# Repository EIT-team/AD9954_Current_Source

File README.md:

# AD9954 communication library

Communication over a serial port to program Analog Devices AD9954 DDS chip.

Arduino source code in _/Program_AD9954_.

Sample MATLAB code for programming over Serial port in _sample_code.m_

Serial commands:

  _frequency xxxx_      frequency to program (Hz)

  _stim 1_              Starts injection
  
  _stim 0_              Stops injection

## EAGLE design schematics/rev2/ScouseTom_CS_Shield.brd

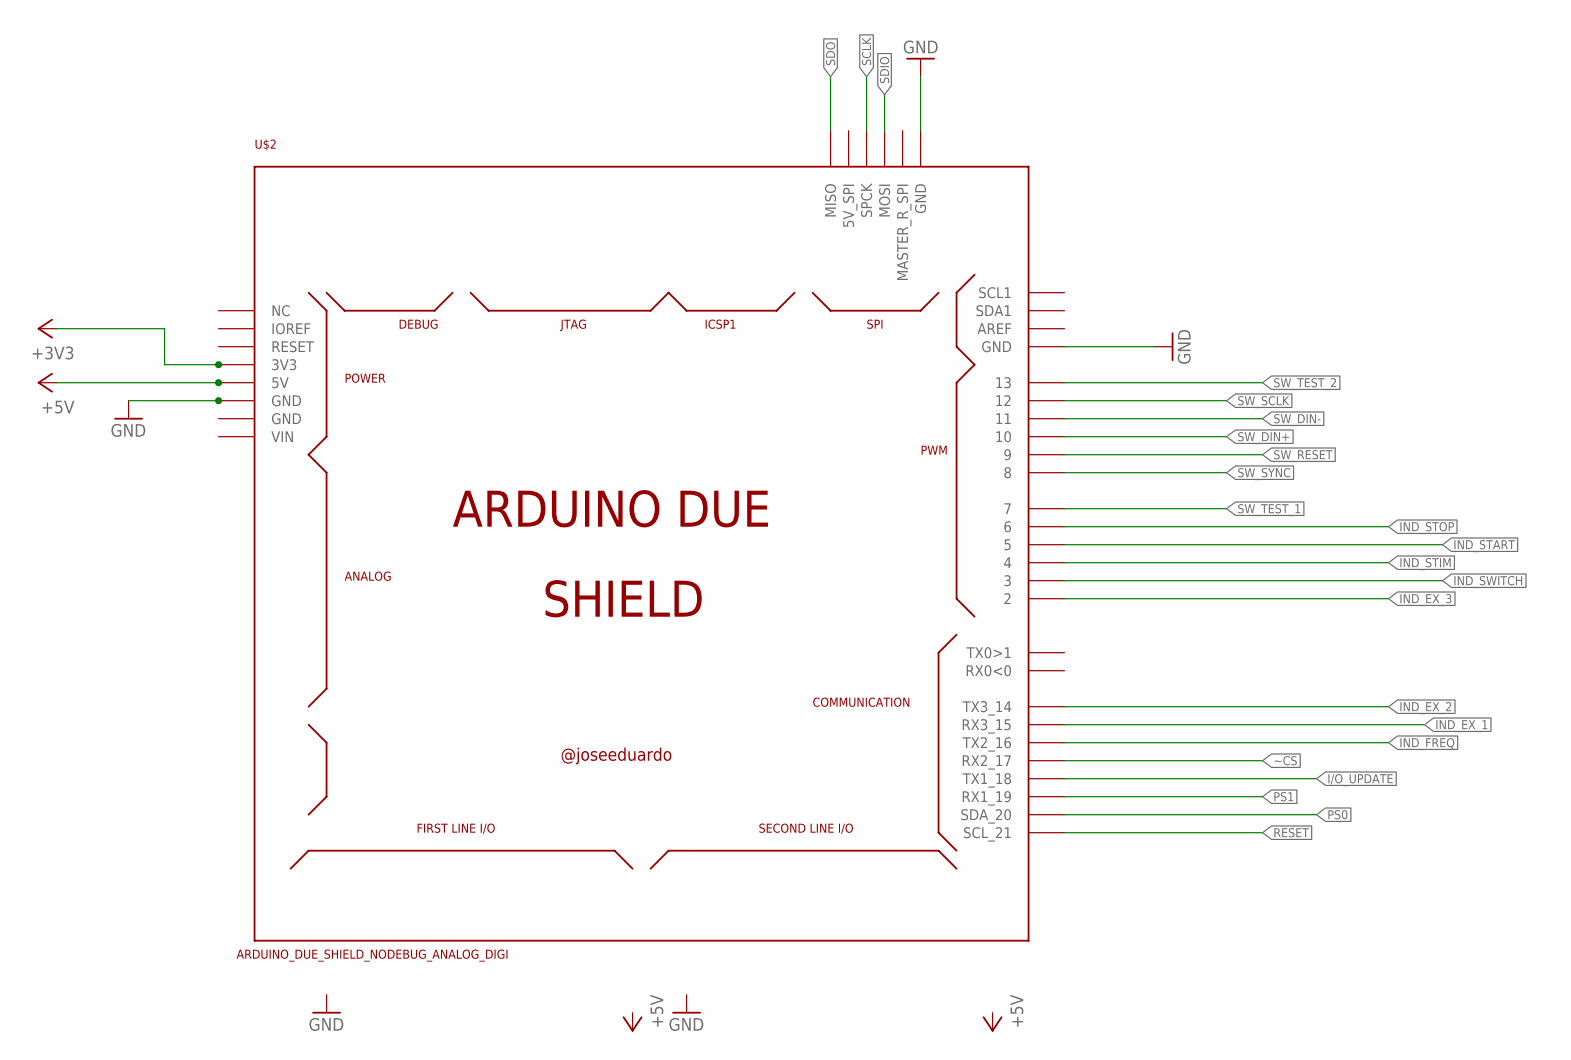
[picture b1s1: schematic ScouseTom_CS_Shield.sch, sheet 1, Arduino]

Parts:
U$2: ARDUINO_DUE_SHIELD_NODEBUG_ANALOG_DIGI; ARDUINO_DUE_SHIELD_NODEBUG_ANALOG_DIG

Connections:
+3V3: U$2.3V3; also elsewhere on the board
+5V: U$2.5V0 (5V); also elsewhere on the board
GND: U$2.GND, U$2.GND_4 (GND), U$2.GND_5 (GND); also elsewhere on the board
I/O_UPDATE: U$2.18 (TX1_18); also elsewhere on the board
IND_EX_1: U$2.15 (RX3_15); also elsewhere on the board
IND_EX_2: U$2.14 (TX3_14); also elsewhere on the board
IND_EX_3: U$2.2; also elsewhere on the board
IND_FREQ: U$2.16 (TX2_16); also elsewhere on the board
IND_START: U$2.5; also elsewhere on the board
IND_STIM: U$2.4; also elsewhere on the board
IND_STOP: U$2.6; also elsewhere on the board
IND_SWITCH: U$2.3; also elsewhere on the board
PS0: U$2.20 (SDA_20); also elsewhere on the board
PS1: U$2.19 (RX1_19); also elsewhere on the board
RESET: U$2.21 (SCL_21); also elsewhere on the board
SCLK: U$2.SPCK; also elsewhere on the board
SDIO: U$2.MOSI; also elsewhere on the board
SDO: U$2.MISO; also elsewhere on the board
SW_DIN+: U$2.10; also elsewhere on the board
SW_DIN-: U$2.11; also elsewhere on the board
SW_RESET: U$2.9; also elsewhere on the board
SW_SCLK: U$2.12; also elsewhere on the board
SW_SYNC: U$2.8; also elsewhere on the board
SW_TEST_1: U$2.7; also elsewhere on the board
SW_TEST_2: U$2.13; also elsewhere on the board
~CS: U$2.17 (RX2_17); also elsewhere on the board

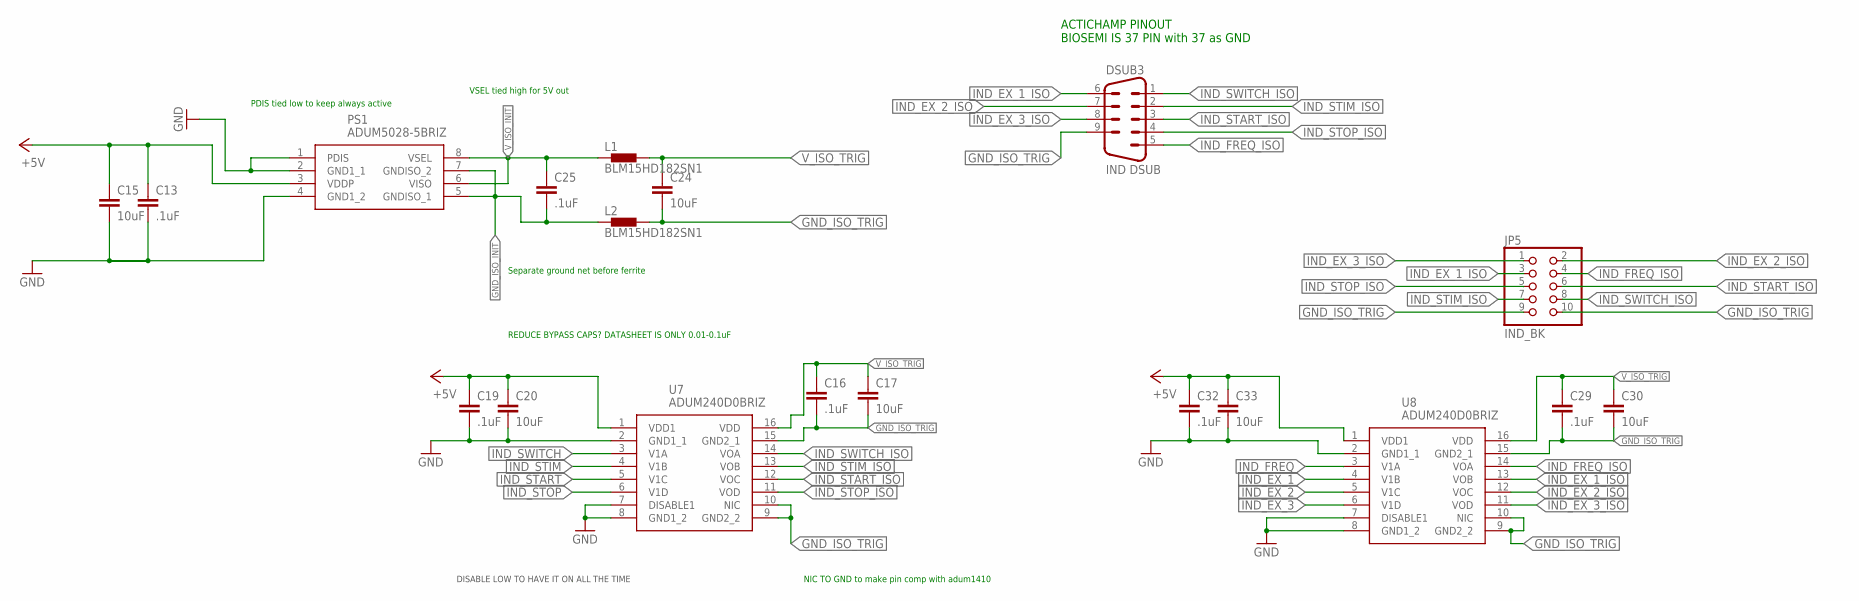
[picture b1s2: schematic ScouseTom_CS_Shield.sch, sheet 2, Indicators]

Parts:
C13, C16, C19, C25, C29, C32: .1uF; C0603
C15, C17, C20, C24, C30, C33: 10uF; C0603
DSUB3: IND DSUB; DSUB9
JP5: IND_BK; 2X05
L1, L2: BLM15HD182SN1; 0402
PS1: ADUM5028-5BRIZ; SOIC127P1031X265-8N
U7, U8: ADUM240D0BRIZ; SOIC127P1032X265-16N

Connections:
+5V: C13.1, C15.1, C19.1, C20.1, C32.1, C33.1, PS1.3 (VDDP), U7.1 (VDD1), U8.1 (VDD1); also elsewhere on the board
GND: C13.2, C15.2, C19.2, C20.2, C32.2, C33.2, PS1.1 (PDIS), PS1.2 (GND1_1), PS1.4 (GND1_2), U7.2 (GND1_1), U7.7 (DISABLE1), U7.8 (GND1_2), U8.2 (GND1_1), U8.7 (DISABLE1), U8.8 (GND1_2); also elsewhere on the board
GND_ISO_INIT: C25.2, L2.1, PS1.5 (GNDISO_1), PS1.7 (GNDISO_2)
GND_ISO_TRIG: C16.2, C17.2, C24.2, C29.2, C30.2, DSUB3.9, JP5.9, JP5.10, L2.2, U7.9 (GND2_2), U7.10 (NIC), U7.15 (GND2_1), U8.9 (GND2_2), U8.10 (NIC), U8.15 (GND2_1)
IND_EX_1: U8.4 (V1B); also elsewhere on the board
IND_EX_1_ISO: DSUB3.6, JP5.3, U8.13 (VOB)
IND_EX_2: U8.5 (V1C); also elsewhere on the board
IND_EX_2_ISO: DSUB3.7, JP5.2, U8.12 (VOC)
IND_EX_3: U8.6 (V1D); also elsewhere on the board
IND_EX_3_ISO: DSUB3.8, JP5.1, U8.11 (VOD)
IND_FREQ: U8.3 (V1A); also elsewhere on the board
IND_FREQ_ISO: DSUB3.5, JP5.4, U8.14 (VOA)
IND_START: U7.5 (V1C); also elsewhere on the board
IND_START_ISO: DSUB3.3, JP5.6, U7.12 (VOC)
IND_STIM: U7.4 (V1B); also elsewhere on the board
IND_STIM_ISO: DSUB3.2, JP5.7, U7.13 (VOB)
IND_STOP: U7.6 (V1D); also elsewhere on the board
IND_STOP_ISO: DSUB3.4, JP5.5, U7.11 (VOD)
IND_SWITCH: U7.3 (V1A); also elsewhere on the board
IND_SWITCH_ISO: DSUB3.1, JP5.8, U7.14 (VOA)
V_ISO_INIT: C25.1, L1.1, PS1.6 (VISO), PS1.8 (VSEL)
V_ISO_TRIG: C16.1, C17.1, C24.1, C29.1, C30.1, L1.2, U7.16 (VDD), U8.16 (VDD)

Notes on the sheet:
ACTICHAMP PINOUT BIOSEMI IS 37 PIN with 37 as GND
NIC TO GND to make pin comp with adum1410
REDUCE BYPASS CAPS? DATASHEET IS ONLY 0.01-0.1uF
PDIS tied low to keep always active
VSEL tied high for 5V out
Separate ground net before ferrite
DISABLE LOW TO HAVE IT ON ALL THE TIME

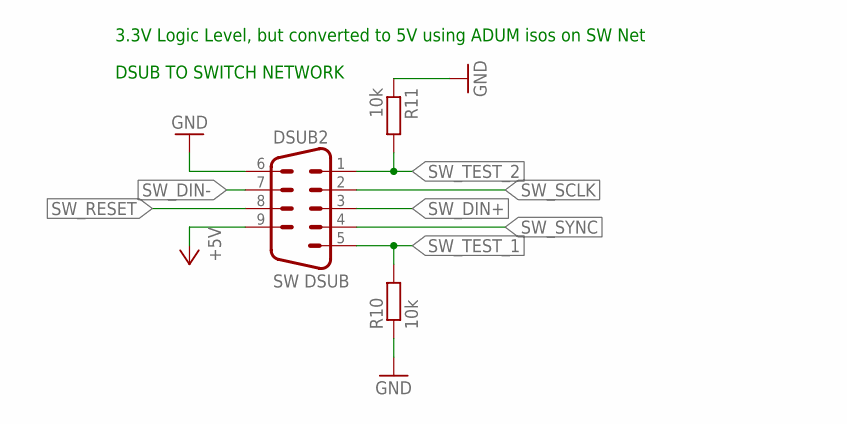
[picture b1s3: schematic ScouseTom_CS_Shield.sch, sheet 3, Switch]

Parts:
DSUB2: SW DSUB; DSUB9
R10, R11: 10k; R0805

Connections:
+5V: DSUB2.9; also elsewhere on the board
GND: DSUB2.6, R10.1, R11.1; also elsewhere on the board
SW_DIN+: DSUB2.3; also elsewhere on the board
SW_DIN-: DSUB2.7; also elsewhere on the board
SW_RESET: DSUB2.8; also elsewhere on the board
SW_SCLK: DSUB2.2; also elsewhere on the board
SW_SYNC: DSUB2.4; also elsewhere on the board
SW_TEST_1: DSUB2.5, R10.2; also elsewhere on the board
SW_TEST_2: DSUB2.1, R11.2; also elsewhere on the board

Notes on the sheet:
DSUB TO SWITCH NETWORK
3.3V Logic Level, but converted to 5V using ADUM isos on SW Net

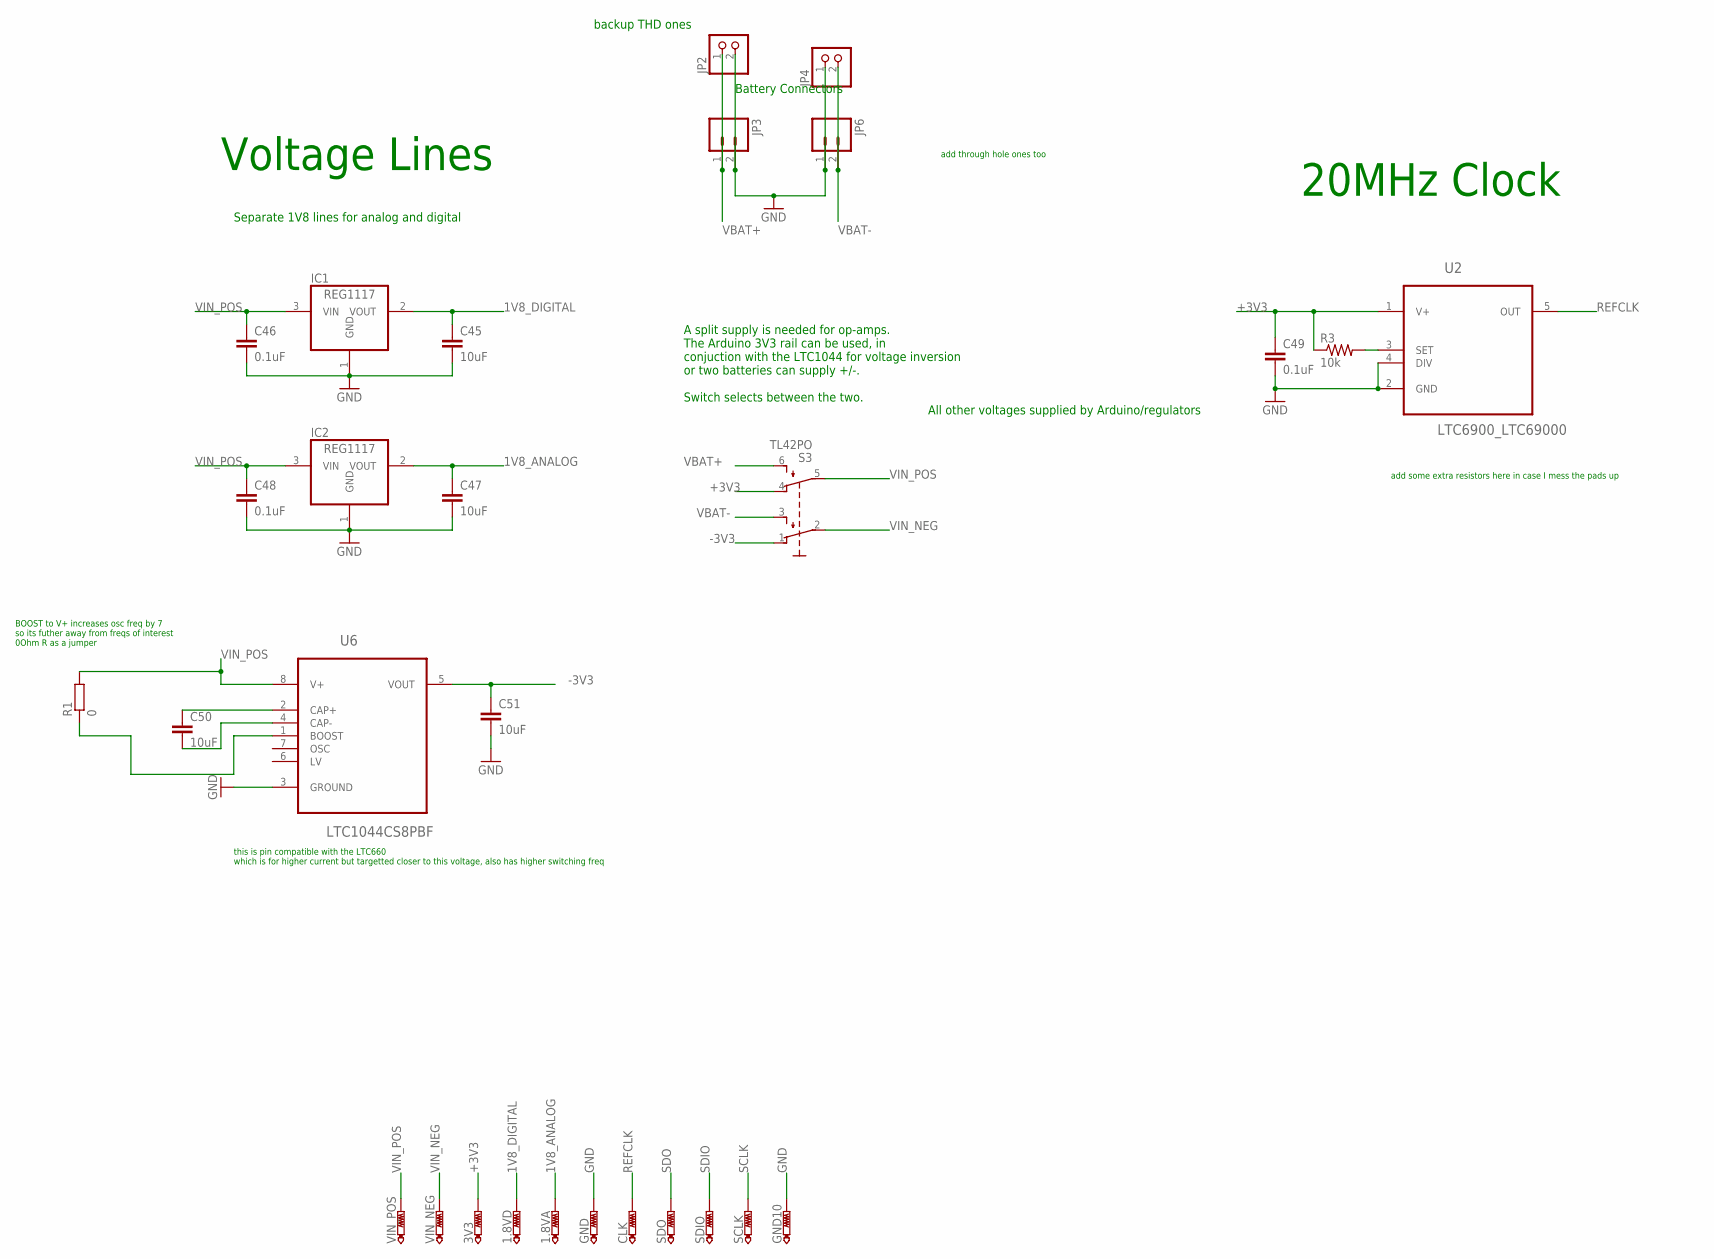
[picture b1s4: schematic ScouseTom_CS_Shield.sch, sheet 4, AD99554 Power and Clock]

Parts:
1.8VA, 1.8VD, 3V3: PTR1PAD1-13; P1-13
C45, C47, C50, C51: 10uF; C0603
C46, C48, C49: 0.1uF; C0603
CLK: PTR1PAD1-13; P1-13
GND, GND10: PTR1PAD1-13; P1-13
IC1, IC2: REG1117; SOT223
JP2, JP4: PINHD-1X2; 1X02
JP3, JP6: M02-JST-2MM-SMT; JST-2-SMD
R1: 0; R0805
R3: 10k; R0805
S3: TL42PO; TL4XPO
SCLK: PTR1PAD1-13; P1-13
SDIO: PTR1PAD1-13; P1-13
SDO: PTR1PAD1-13; P1-13
U2: LTC6900_LTC69000; LTC6900_SOT23-5L
U6: LTC1044CS8PBF; SOIC127P600X175-8N
VIN_NEG: PTR1PAD1-13; P1-13
VIN_POS: PTR1PAD1-13; P1-13

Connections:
1V8_ANALOG: 1.8VA.TP, C47.1, IC2.2 (VOUT); also elsewhere on the board
1V8_DIGITAL: 1.8VD.TP, C45.1, IC1.2 (VOUT); also elsewhere on the board
+3V3: 3V3.TP, C49.1, R3.1, S3.4 (O1), U2.1 (V+); also elsewhere on the board
-3V3: C51.1, S3.1 (O), U6.5 (VOUT)
GND: C45.2, C46.2, C47.2, C48.2, C49.2, C51.2, GND.TP, GND10.TP, IC1.1 (GND), IC2.1 (GND), JP2.2, JP3.2, JP4.1, JP6.1, U2.2 (GND), U2.4 (DIV), U6.3 (GROUND); also elsewhere on the board
unnamed: R1.1, U6.1 (BOOST)
unnamed: C50.1, U6.2 (CAP+)
unnamed: R3.2, U2.3 (SET)
unnamed: C50.2, U6.4 (CAP-)
REFCLK: CLK.TP, U2.5 (OUT); also elsewhere on the board
SCLK: SCLK.TP; also elsewhere on the board
SDIO: SDIO.TP; also elsewhere on the board
SDO: SDO.TP; also elsewhere on the board
VBAT+: JP2.1, JP3.1, S3.6 (S1)
VBAT-: JP4.2, JP6.2, S3.3 (S)
VIN_NEG: S3.2, VIN_NEG.TP; also elsewhere on the board
VIN_POS: C46.1, C48.1, IC1.3 (VIN), IC2.3 (VIN), R1.2, S3.5 (P1), U6.8 (V+), VIN_POS.TP; also elsewhere on the board

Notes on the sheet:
Separate 1V8 lines for analog and digital
Voltage Lines
20MHz Clock
A split supply is needed for op-amps. The Arduino 3V3 rail can be used, in conjuction with the LTC1044 for voltage inversion or two batteries can supply +/-. Switch selects between the two.
Battery Connectors
All other voltages supplied by Arduino/regulators
add some extra resistors here in case I mess the pads up
add through hole ones too
this is pin compatible with the LTC660 which is for higher current but targetted closer to this voltage, also has higher switching freq
BOOST to V+ increases osc freq by 7 so its futher away from freqs of interest 0Ohm R as a jumper
backup THD ones

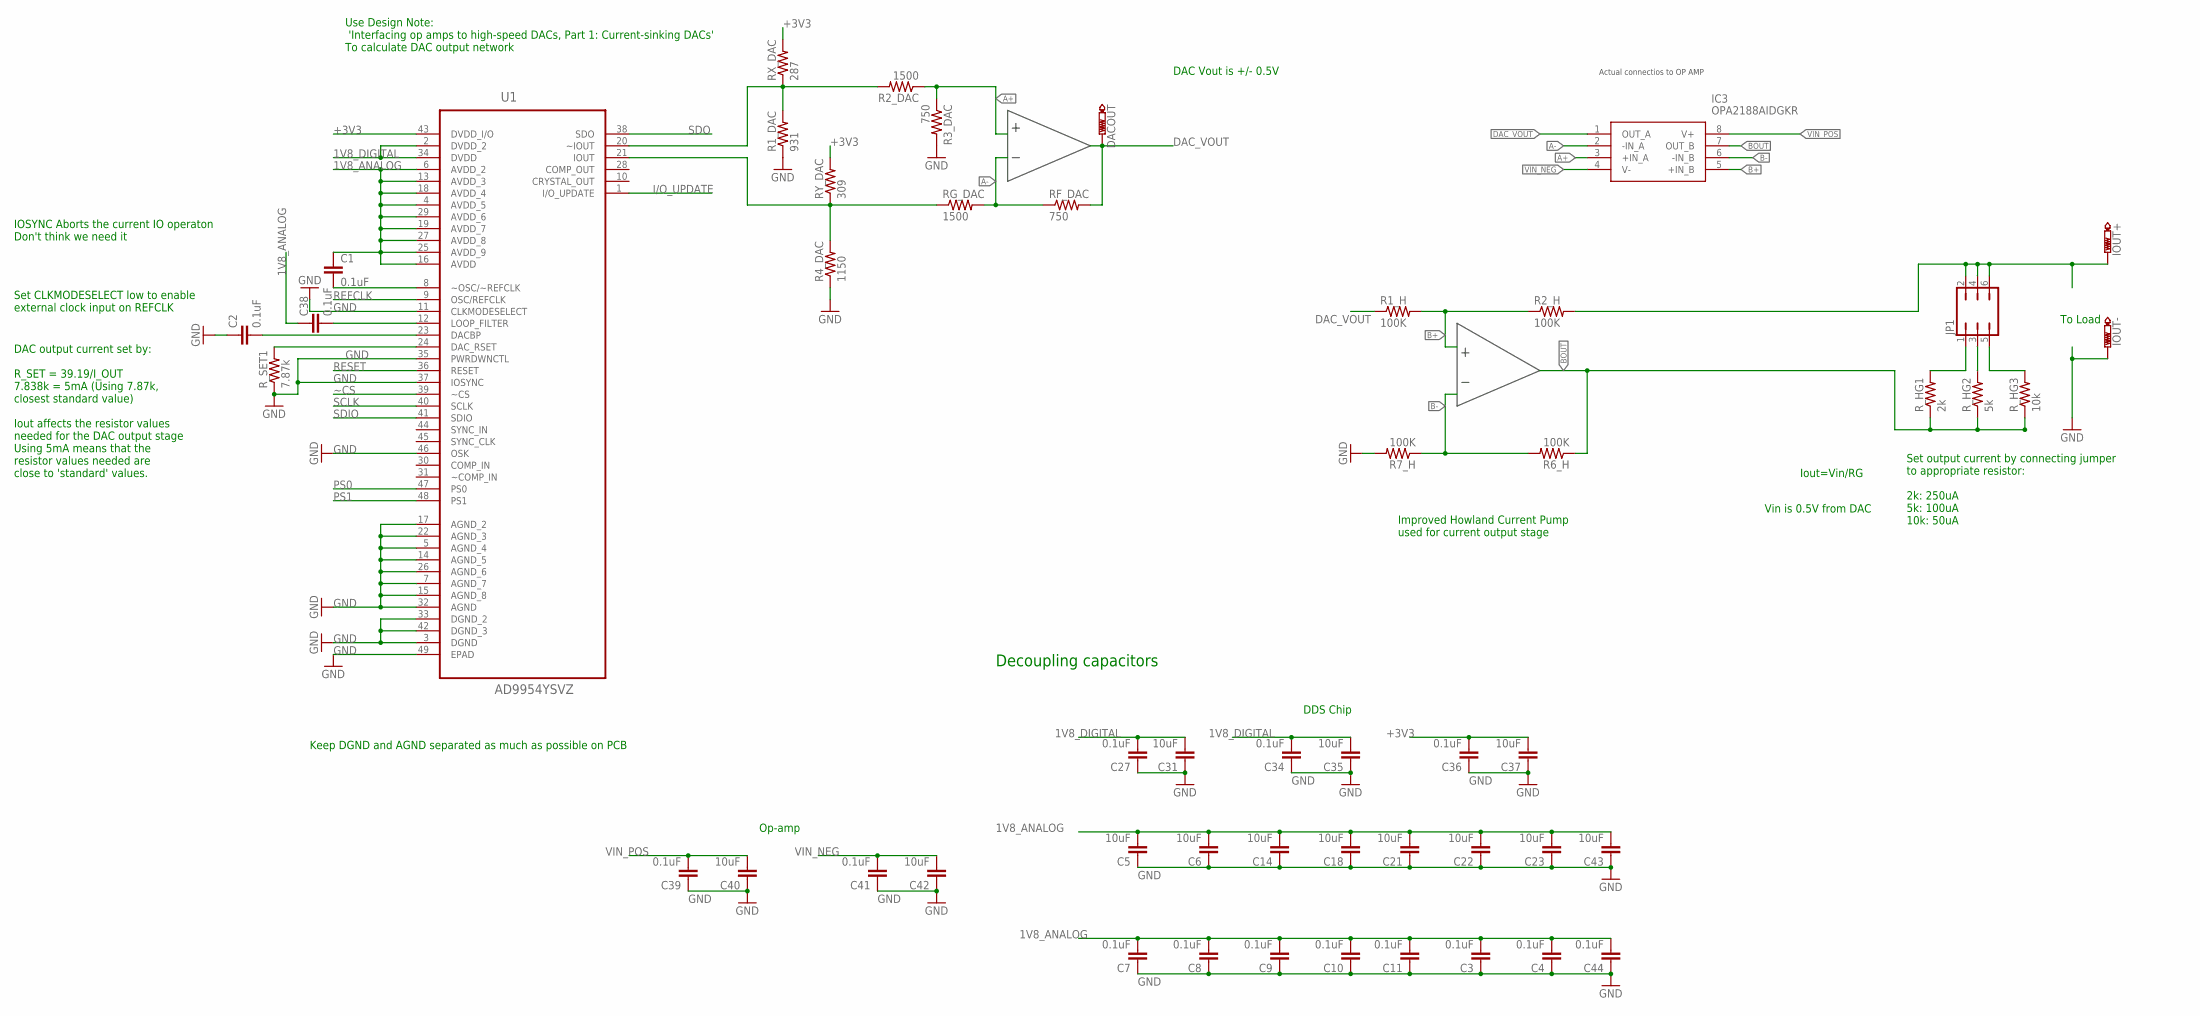
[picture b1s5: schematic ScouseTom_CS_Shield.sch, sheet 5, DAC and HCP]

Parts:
C1, C2, C3, C4, C7, C8, C9, C10, C11, C27, C34, C36, C38, C39, C41, C44: 0.1uF; C0603
C5, C6, C14, C18, C21, C22, C23, C31, C35, C37, C40, C42, C43: 10uF; C0603
DACOUT: PTR1PAD1-13; P1-13
IC3: OPA2188AIDGKR; SOP65P490X110-8N
IOUT+: PTR1PAD1-13; P1-13
IOUT-: PTR1PAD1-13; P1-13
JP1: JP3Q
R1_DAC: 931; R0805
R1_H, R2_H, R6_H, R7_H: 100K; R0805
R2_DAC: 1500; R0805
R3_DAC: 750; R0805
R4_DAC: 1150; R0805
RF_DAC: 750; R0805
RG_DAC: 1500; R0805
RX_DAC: 287; R0805
RY_DAC: 309; R0805
R_HG1: 2k; R0805
R_HG2: 5k; R0805
R_HG3: 10k; R0805
R_SET1: 7.87k; R0805
U1: AD9954YSVZ; QFP50P900X900X120-49N

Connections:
1V8_ANALOG: C1.1, C3.2, C4.2, C5.2, C6.2, C7.2, C8.2, C9.2, C10.2, C11.2, C14.2, C18.2, C21.2, C22.2, C23.2, C38.1, C43.2, C44.2, U1.4 (AVDD_5), U1.6 (AVDD_2), U1.13 (AVDD_3), U1.16 (AVDD), U1.18 (AVDD_4), U1.19 (AVDD_7), U1.25 (AVDD_9), U1.27 (AVDD_8), U1.29 (AVDD_6); also elsewhere on the board
1V8_DIGITAL: C27.2, C31.2, C34.2, C35.2, U1.2 (DVDD_2), U1.34 (DVDD); also elsewhere on the board
+3V3: C36.2, C37.2, RX_DAC.2, RY_DAC.2, U1.43 (DVDD_I/O); also elsewhere on the board
A+: IC3.3 (+IN_A), R2_DAC.1, R3_DAC.1
A-: IC3.2 (-IN_A), RF_DAC.1, RG_DAC.2
B+: IC3.5 (+IN_B), R1_H.2, R2_H.1
B-: IC3.6 (-IN_B), R6_H.2, R7_H.1
BOUT: IC3.7 (OUT_B), R6_H.1, R_HG1.1, R_HG2.1, R_HG3.1
DAC_VOUT: DACOUT.TP, IC3.1 (OUT_A), R1_H.1, RF_DAC.2
GND: C2.1, C3.1, C4.1, C5.1, C6.1, C7.1, C8.1, C9.1, C10.1, C11.1, C14.1, C18.1, C21.1, C22.1, C23.1, C27.1, C31.1, C34.1, C35.1, C36.1, C37.1, C39.1, C40.1, C41.1, C42.1, C43.1, C44.1, IOUT-.TP, R1_DAC.1, R3_DAC.2, R4_DAC.1, R7_H.2, R_SET1.1, U1.3 (DGND), U1.5 (AGND_4), U1.7 (AGND_7), U1.11 (CLKMODESELECT), U1.14 (AGND_5), U1.15 (AGND_8), U1.17 (AGND_2), U1.22 (AGND_3), U1.26 (AGND_6), U1.32 (AGND), U1.33 (DGND_2), U1.35 (PWRDWNCTL), U1.37 (IOSYNC), U1.42 (DGND_3), U1.46 (OSK), U1.49 (EPAD); also elsewhere on the board
I/O_UPDATE: U1.1 (I/O_UPDATE); also elsewhere on the board
IOUT: R4_DAC.2, RG_DAC.1, RY_DAC.1, U1.21 (IOUT)
unnamed: C2.2, U1.23 (DACBP)
unnamed: C1.2, U1.8 (~OSC/~REFCLK)
unnamed: R_SET1.2, U1.24 (DAC_RSET)
unnamed: C38.2, U1.12 (LOOP_FILTER)
unnamed: IOUT+.TP, JP1.2, JP1.4, JP1.6, R2_H.2
unnamed: JP1.3, R_HG2.2
unnamed: JP1.5, R_HG3.2
unnamed: JP1.1, R_HG1.2
PS0: U1.47 (PS0); also elsewhere on the board
PS1: U1.48 (PS1); also elsewhere on the board
REFCLK: U1.9 (OSC/REFCLK); also elsewhere on the board
RESET: U1.36 (RESET); also elsewhere on the board
SCLK: U1.40 (SCLK); also elsewhere on the board
SDIO: U1.41 (SDIO); also elsewhere on the board
SDO: U1.38 (SDO); also elsewhere on the board
VIN_NEG: C41.2, C42.2, IC3.4 (V-); also elsewhere on the board
VIN_POS: C39.2, C40.2, IC3.8 (V+); also elsewhere on the board
~CS: U1.39 (~CS); also elsewhere on the board
~IOUT: R1_DAC.2, R2_DAC.2, RX_DAC.1, U1.20 (~IOUT)

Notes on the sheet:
Set CLKMODESELECT low to enable external clock input on REFCLK
DAC output current set by: R_SET = 39.19/I_OUT 7.838k = 5mA (Using 7.87k, closest standard value) Iout affects the resistor values needed for the DAC output stage Using 5mA means that the resistor values needed are close to 'standard' values.
IOSYNC Aborts the current IO operaton Don't think we need it
Decoupling capacitors
Use Design Note: 'Interfacing op amps to high-speed DACs, Part 1: Current-sinking DACs' To calculate DAC output network
Keep DGND and AGND separated as much as possible on PCB
DAC Vout is +/- 0.5V
DDS Chip
Op-amp
Set output current by connecting jumper to appropriate resistor: 2k: 250uA 5k: 100uA 10k: 50uA
To Load
Improved Howland Current Pump used for current output stage
Actual connectios to OP AMP
Iout=Vin/RG
Vin is 0.5V from DAC

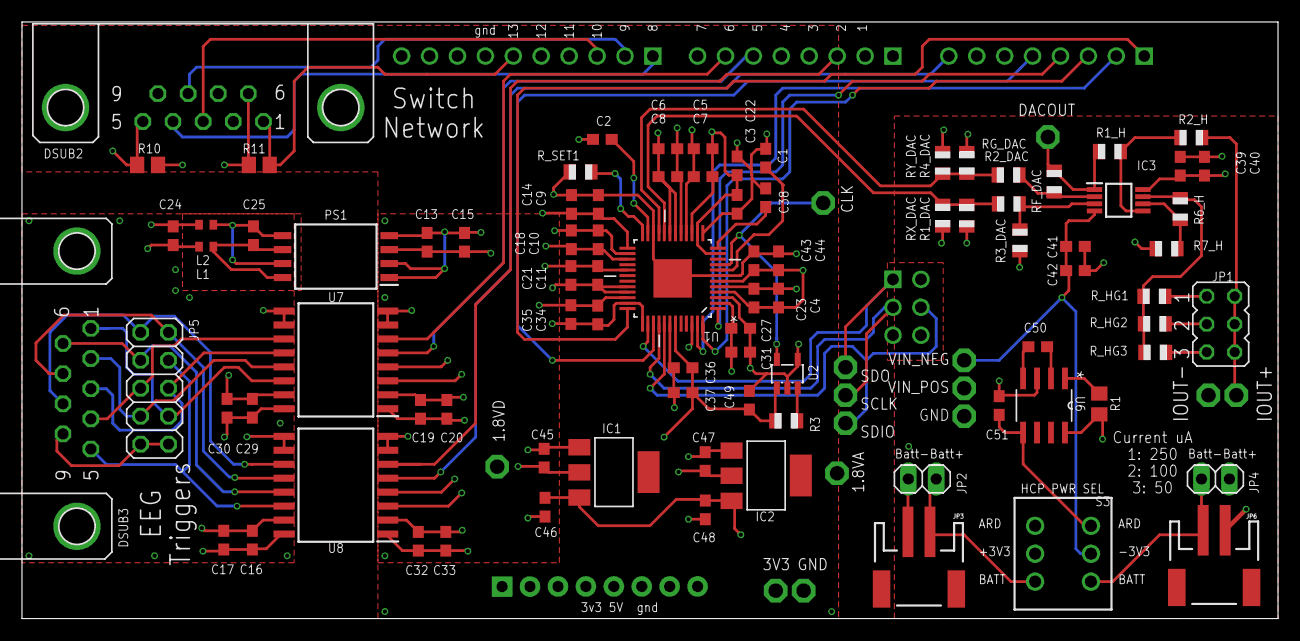
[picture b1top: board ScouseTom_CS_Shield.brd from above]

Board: 4 copper layers, 114.3 x 54.3 mm, 103 parts (0 on the bottom side), 66 nets.

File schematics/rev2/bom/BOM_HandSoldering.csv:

"Qty";"Value";"Device";"Package";"Parts";"Description";"DESCRIPTION";"HEIGHT";"MANUFACTURER_NAME";"MANUFACTURER_PART_NUMBER";"MF";"MOUSER_PART_NUMBER";"MOUSER_PRICE-STOCK";"MPN";"OC_FARNELL";"OC_NEWARK";"PACKAGE";"POPULARITY";"RS_PART_NUMBER";"RS_PRICE-STOCK";"SPICEPREFIX";"SUPPLIER";"TP_SIGNAL_NAME";
"1";"";"JP3Q";"JP3Q";"JP1";"JUMPER";"";"";"";"";"";"";"";"";"";"";"";"";"";"";"";"";"";
"2";"";"M02-JST-2MM-SMT";"JST-2-SMD";"JP3, JP6";"Header 2";"";"";"";"";"";"";"";"";"";"";"";"";"";"";"";"";"";
"2";"";"PINHD-1X2";"1X02";"JP2, JP4";"PIN HEADER";"";"";"";"";"";"";"";"";"";"";"";"";"";"";"";"";"";
"6";".1uF";"C-EUC0603";"C0603";"C13, C16, C19, C25, C29, C32";"CAPACITOR, European symbol";"";"";"";"";"";"";"";"";"";"";"";"";"";"";"";"";"";
"1";"0";"R-EU_R0805";"R0805";"R1";"RESISTOR, European symbol";"";"";"";"";"";"";"";"";"";"";"";"";"";"";"";"";"";
"19";"0.1uF";"C-EUC0603";"C0603";"C1, C2, C3, C4, C7, C8, C9, C10, C11, C27, C34, C36, C38, C39, C41, C44, C46, C48, C49";"CAPACITOR, European symbol";"";"";"";"";"";"";"";"";"";"";"";"";"";"";"";"";"";
"4";"100K";"R-US_R0805";"R0805";"R1_H, R2_H, R6_H, R7_H";"RESISTOR, American symbol";"";"";"";"";"";"";"";"";"";"";"";"";"";"";"";"";"";
"2";"10k";"R-US_R0805";"R0805";"R10, R11";"RESISTOR, American symbol";"";"";"";"";"";"";"";"";"";"";"";"85";"";"";"R";"";"";
"2";"10k";"R-US_R0805";"R0805";"R3, R_HG3";"RESISTOR, American symbol";"";"";"";"";"";"";"";"";"";"";"";"";"";"";"";"";"";
"23";"10uF";"C-EUC0603";"C0603";"C5, C6, C14, C15, C17, C18, C20, C21, C22, C23, C24, C30, C31, C33, C35, C37, C40, C42, C43, C45, C47, C50, C51";"CAPACITOR, European symbol";"";"";"";"";"";"";"";"";"";"";"";"";"";"";"";"";"";
"1";"161";"R-US_R0805";"R0805";"RX_DAC";"RESISTOR, American symbol";"";"";"";"";"";"";"";"";"";"";"";"";"";"";"";"";"";
"1";"177";"R-US_R0805";"R0805";"RY_DAC";"RESISTOR, American symbol";"";"";"";"";"";"";"";"";"";"";"";"";"";"";"";"";"";
"4";"1k";"R-US_R0805";"R0805";"R2_DAC, R3_DAC, RF_DAC, RG_DAC";"RESISTOR, American symbol";"";"";"";"";"";"";"";"";"";"";"";"";"";"";"";"";"";
"1";"2k";"R-US_R0805";"R0805";"R_HG1";"RESISTOR, American symbol";"";"";"";"";"";"";"";"";"";"";"";"";"";"";"";"";"";
"1";"304";"R-US_R0805";"R0805";"R1_DAC";"RESISTOR, American symbol";"";"";"";"";"";"";"";"";"";"";"";"";"";"";"";"";"";
"1";"353";"R-US_R0805";"R0805";"R4_DAC";"RESISTOR, American symbol";"";"";"";"";"";"";"";"";"";"";"";"";"";"";"";"";"";
"1";"5k";"R-US_R0805";"R0805";"R_HG2";"RESISTOR, American symbol";"";"";"";"";"";"";"";"";"";"";"";"";"";"";"";"";"";
"1";"7.87k";"R-US_R0805";"R0805";"R_SET1";"RESISTOR, American symbol";"";"";"";"";"";"";"";"";"";"";"";"";"";"";"";"";"";
"1";"AD9954YSVZ";"AD9954YSVZ";"QFP50P900X900X120-49N";"U1";"Direct Digital Synthesizer";"";"";"";"";"";"";"";"AD9954YSVZ";"1581969";"19M8953";"TQFP-48";"";"";"";"";"ANALOG DEVICES";"";
"2";"ADUM240D0BRIZ";"ADUM240D0BRIZ";"SOIC127P1032X265-16N";"U7, U8";"Digital Isolator CMOS 4-CH 150Mbps 16-Pin SOIC W Tube";"Digital Isolator CMOS 4-CH 150Mbps 16-Pin SOIC W Tube";"2.65mm";"Analog Devices";"ADUM240D0BRIZ";"";"";"";"";"";"";"";"";"";"";"";"";"";
"1";"ADUM5028-5BRIZ";"ADUM5028-5BRIZ";"SOIC127P1031X265-8N";"PS1";"Switching Voltage Regulators isoPower 3kV,";"Switching Voltage Regulators isoPower 3kV,";"2.65mm";"Analog Devices";"ADUM5028-5BRIZ";"";"584-ADUM5028-5BRIZ";"https://www.mouser.com/Search/Refine.aspx?Keyword=584-ADUM50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";"";"";"";"";"";"";"";"";"";"";
"1";"ARDUINO_DUE_SHIELD_NODEBUG_ANALOG_DIGI";"ARDUINO_DUE_SHIELD_NODEBUG_ANALOG_DIGI";"ARDUINO_DUE_SHIELD_NODEBUG_ANALOG_DIG";"U$2";"";"";"";"";"";"";"";"";"";"";"";"";"";"";"";"";"";"";
"2";"BLM15HD182SN1";"BLM15HD182SN1";"0402";"L1, L2";"EMIFIL (R) Chip Ferrite Bead for GHz Noise";"";"";"";"";"";"";"";"";"";"";"";"";"";"";"";"";"";
"1";"IND DSUB";"DSUB9RA";"DSUB9";"DSUB3";"";"";"";"";"";"";"";"";"";"";"";"";"";"";"";"";"";"";
"1";"IND_BK";"PINHD-2X5";"2X05";"JP5";"PIN HEADER";"";"";"";"";"";"";"";"";"";"";"";"";"";"";"";"";"";
"1";"LTC1044CS8PBF";"LTC1044CS8PBF";"SOIC127P600X175-8N";"U6";"Switched Capacitor Voltage Converter";"";"";"";"";"";"";"";"LTC1044CS8#PBF";"1663593";"55M8900";"SOIC-8";"";"";"";"";"Linear Technology";"";
"1";"LTC6900_LTC69000";"LTC6900_LTC69000";"LTC6900_SOT23-5L";"U2";"Low Power, 1kHz to 20MHz";"";"";"";"";"";"";"";"";"";"";"";"";"";"";"";"";"";
"1";"OPA2188AIDGKR";"OPA2188AIDGKR";"SOP65P490X110-8N";"IC3";"0.03V/C, 6V Vos, Low Noise, Rail-to-Rail Output, 36V Zero-Drift Operational Amplifier";"0.03V/C, 6V Vos, Low Noise, Rail-to-Rail Output, 36V Zero-Drift Operational Amplifier";"1.1mm";"Texas Instruments";"OPA2188AIDGKR";"";"";"";"";"";"";"";"";"";"";"";"";"";
"14";"PTR1PAD1-13";"PTR1PAD1-13";"P1-13";"1.8VA, 1.8VD, 3V3, CLK, DACOUT, GND, GND10, IOUT+, IOUT-, SCLK, SDIO, SDO, VIN_NEG, VIN_POS";"TEST PIN";"";"";"";"";"";"";"";"";"";"";"";"";"";"";"";"";"";
"2";"REG1117";"REG1117";"SOT223";"IC1, IC2";"800mA and 1A Low Dropout (LDO) Positive Regulator";"";"";"";"";"";"";"";"REG1117";"1097566";"14P6981";"";"";"";"";"";"";"";
"1";"SW DSUB";"DSUB9RA";"DSUB9";"DSUB2";"";"";"";"";"";"";"";"";"";"";"";"";"";"";"";"";"";"";
"1";"TL42PO";"TL42PO";"TL4XPO";"S3";"TINY SWITCH ON - MOM";"";"";"";"";"";"";"";"";"";"";"";"";"";"";"";"";"";

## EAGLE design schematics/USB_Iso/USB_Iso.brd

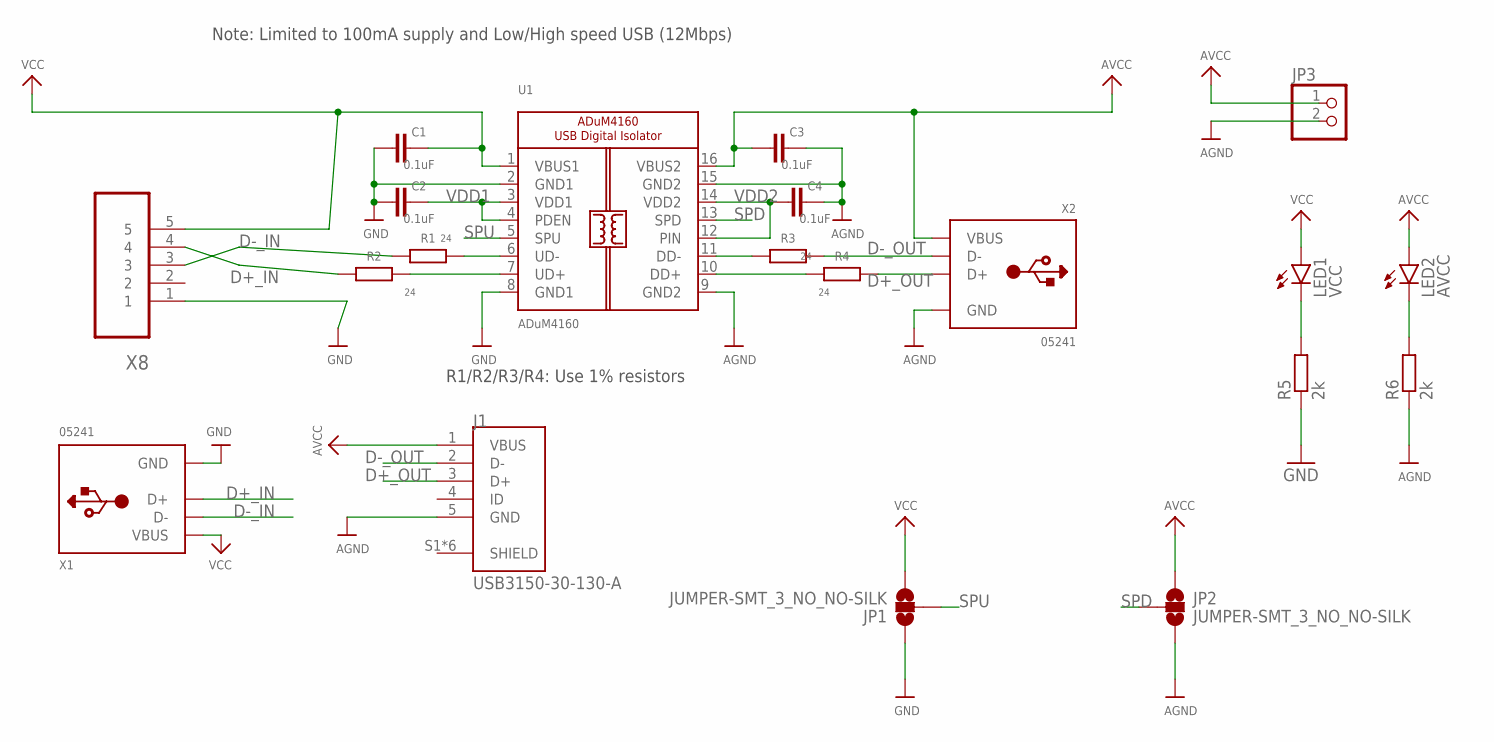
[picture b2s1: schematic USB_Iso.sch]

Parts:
C1, C2, C3, C4: 0.1uF; C0603
J1: USB3150-30-130-A; GCT_USB3150-30-130-A
JP1, JP2: JUMPER-SMT_3_NO_NO-SILK; SMT-JUMPER_3_NO_NO-SILK
JP3: PINHD-1X2; 1X02
LED1: VCC; CHIP-LED0805
LED2: AVCC; CHIP-LED0805
R1, R2, R3, R4: 24; R0603
R5, R6: 2k; R0805
U1: ADuM4160; SOIC16WIDE
X1, X2: 05241; USB_HOST-PTH
X8: 47346-0001; MOLEX_47346-0001

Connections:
AGND: C3.1, C4.1, J1.5 (GND), JP2.3, JP3.2, R6.1, U1.9 (GND2), U1.15 (GND2), X2.GND
AVCC: C3.2, J1.1 (VBUS), JP2.1, JP3.1, LED2.A, U1.16 (VBUS2), X2.VBUS
D+_IN: R2.1, X1.D+, X8.4
D+_OUT: J1.3 (D+), R4.2, X2.D+
D-_IN: R1.1, X1.D-, X8.3
D-_OUT: J1.2 (D-), R3.2, X2.D-
GND: C1.2, C2.2, JP1.1, R5.1, U1.2 (GND1), U1.8 (GND1), X1.GND, X8.1
unnamed: LED1.C, R5.2
unnamed: R2.2, U1.7 (UD+)
unnamed: R1.2, U1.6 (UD-)
unnamed: LED2.C, R6.2
unnamed: R4.1, U1.10 (DD+)
unnamed: R3.1, U1.11 (DD-)
SPD: JP2.2, U1.13 (SPD)
SPU: JP1.2, U1.5 (SPU)
VCC: C1.1, JP1.3, LED1.A, U1.1 (VBUS1), X1.VBUS, X8.5
VDD1: C2.1, U1.3 (VDD1), U1.4 (PDEN)
VDD2: C4.2, U1.12 (PIN), U1.14 (VDD2)

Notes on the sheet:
R1/R2/R3/R4: Use 1% resistors
Note: Limited to 100mA supply and Low/High speed USB (12Mbps)

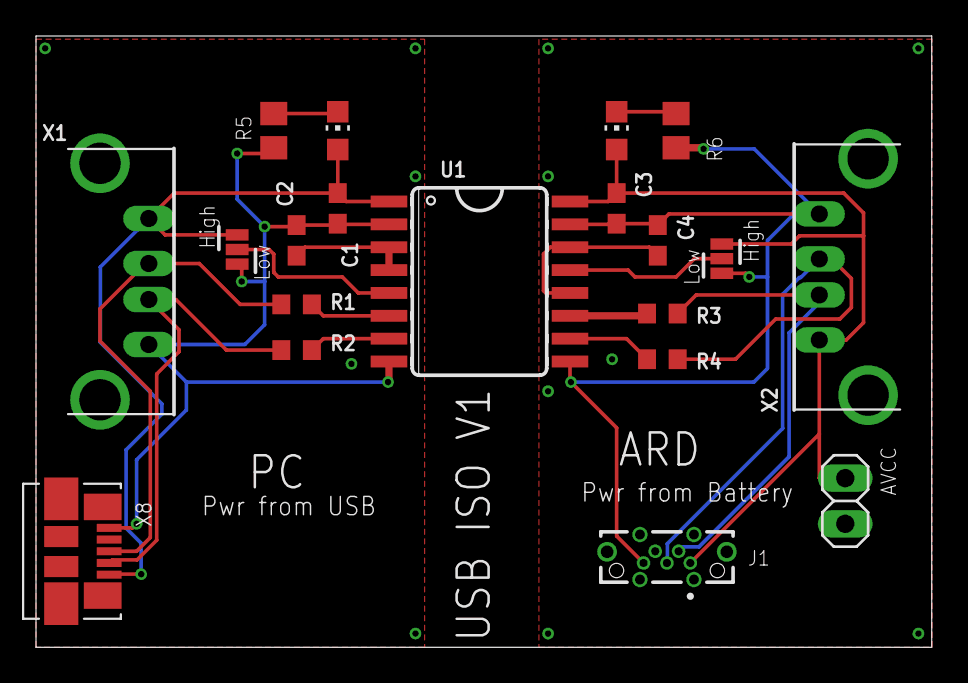
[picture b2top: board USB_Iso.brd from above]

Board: 2 copper layers, 49.8 x 34.0 mm, 20 parts (0 on the bottom side), 18 nets.

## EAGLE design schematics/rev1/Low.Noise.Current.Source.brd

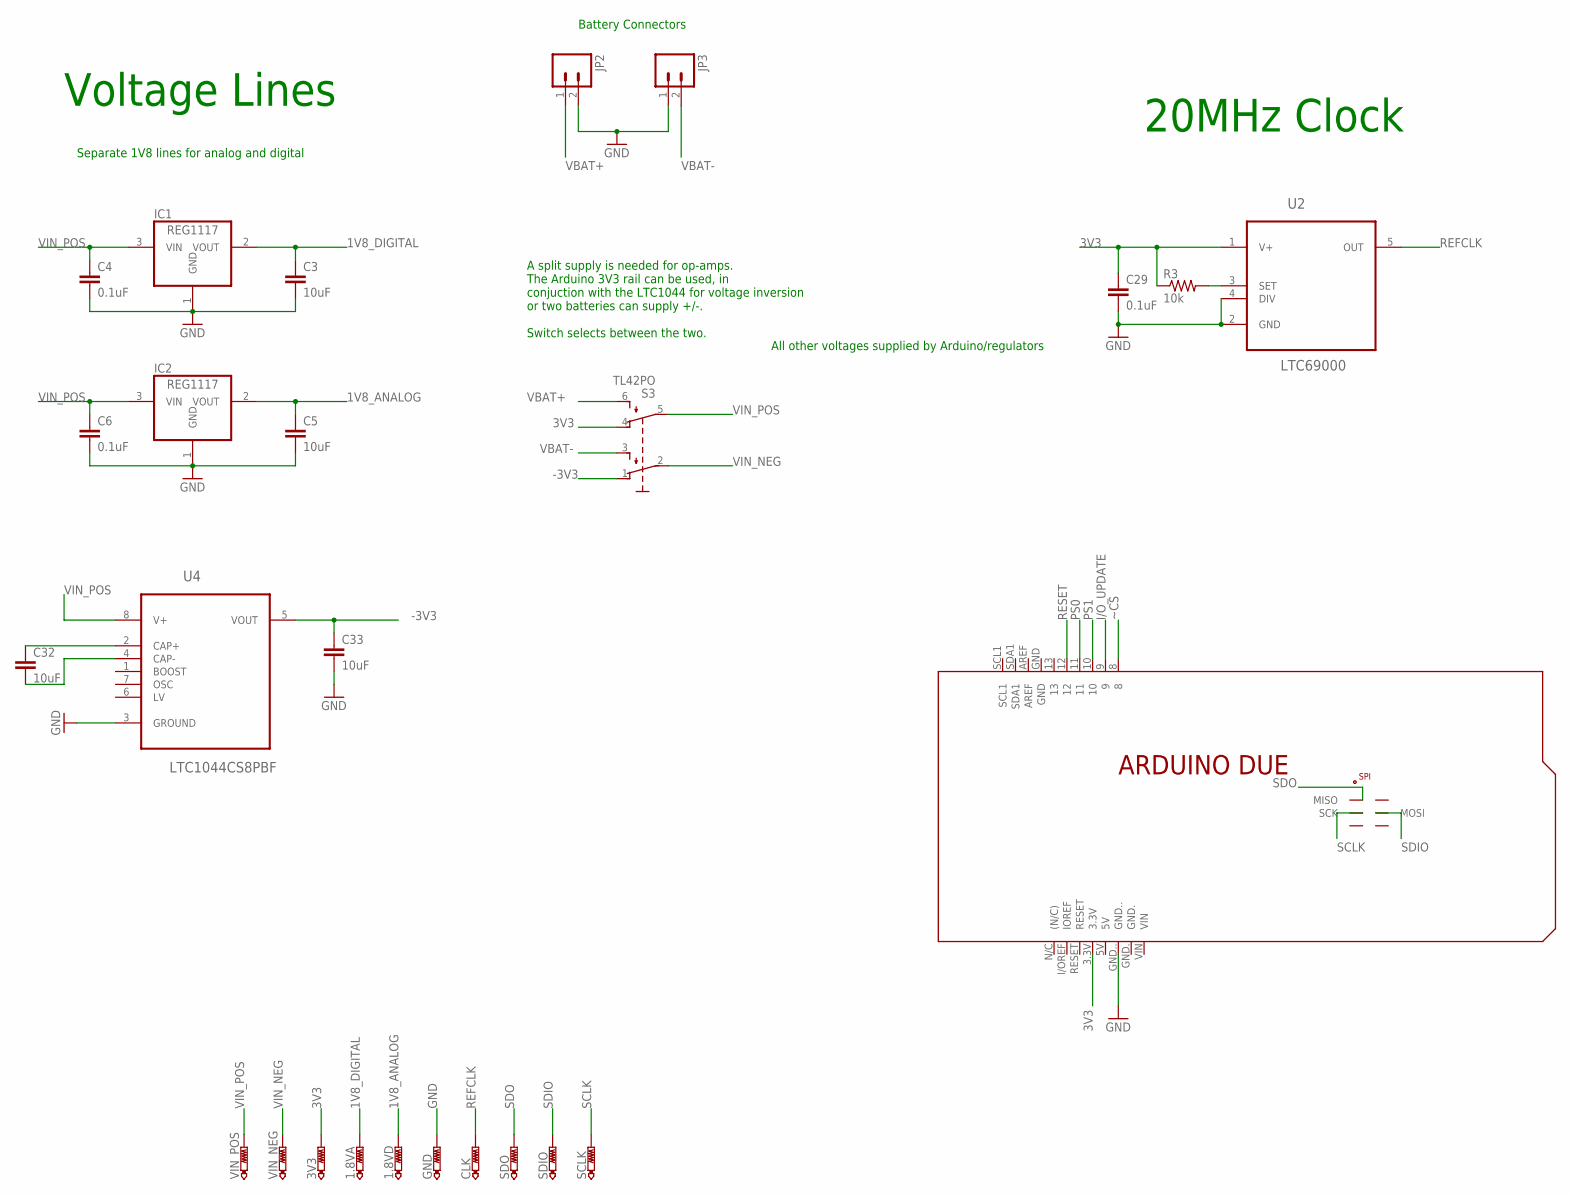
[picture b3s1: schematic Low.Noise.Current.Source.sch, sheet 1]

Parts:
1.8VA, 1.8VD, 3V3: PTR1PAD1-13; P1-13
C3, C5, C32, C33: 10uF; C0603
C4, C6, C29: 0.1uF; C0603
CLK: PTR1PAD1-13; P1-13
GND: PTR1PAD1-13; P1-13
IC1, IC2: REG1117; SOT223
JP2, JP3: M02-JST-2MM-SMT; JST-2-SMD
PCB1: ARDUINO_DUE
R3: 10k; R0805
S3: TL42PO; TL4XPO
SCLK: PTR1PAD1-13; P1-13
SDIO: PTR1PAD1-13; P1-13
SDO: PTR1PAD1-13; P1-13
U2: LTC69000; SOT23-5L
U4: LTC1044CS8PBF; SOIC127P600X175-8N
VIN_NEG: PTR1PAD1-13; P1-13
VIN_POS: PTR1PAD1-13; P1-13

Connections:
1V8_ANALOG: 1.8VD.TP, C5.1, IC2.2 (VOUT); also elsewhere on the board
1V8_DIGITAL: 1.8VA.TP, C3.1, IC1.2 (VOUT); also elsewhere on the board
3V3: 3V3.TP, C29.1, PCB1.3.3V, R3.1, S3.4 (O1), U2.1 (V+); also elsewhere on the board
-3V3: C33.1, S3.1 (O), U4.5 (VOUT)
GND: C3.2, C4.2, C5.2, C6.2, C29.2, C33.2, GND.TP, IC1.1 (GND), IC2.1 (GND), JP2.2, JP3.1, PCB1.GND.., U2.2 (GND), U2.4 (DIV), U4.3 (GROUND); also elsewhere on the board
I/O_UPDATE: PCB1.9; also elsewhere on the board
unnamed: C32.1, U4.2 (CAP+)
unnamed: R3.2, U2.3 (SET)
unnamed: C32.2, U4.4 (CAP-)
PS0: PCB1.11; also elsewhere on the board
PS1: PCB1.10; also elsewhere on the board
REFCLK: CLK.TP, U2.5 (OUT); also elsewhere on the board
RESET: PCB1.12; also elsewhere on the board
SCLK: PCB1.SCK, SCLK.TP; also elsewhere on the board
SDIO: PCB1.MOSI, SDIO.TP; also elsewhere on the board
SDO: PCB1.MISO, SDO.TP; also elsewhere on the board
VBAT+: JP2.1, S3.6 (S1)
VBAT-: JP3.2, S3.3 (S)
VIN_NEG: S3.2, VIN_NEG.TP; also elsewhere on the board
VIN_POS: C4.1, C6.1, IC1.3 (VIN), IC2.3 (VIN), S3.5 (P1), U4.8 (V+), VIN_POS.TP; also elsewhere on the board
~CS: PCB1.8; also elsewhere on the board

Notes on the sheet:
Separate 1V8 lines for analog and digital
Voltage Lines
20MHz Clock
A split supply is needed for op-amps. The Arduino 3V3 rail can be used, in conjuction with the LTC1044 for voltage inversion or two batteries can supply +/-. Switch selects between the two.
Battery Connectors
All other voltages supplied by Arduino/regulators

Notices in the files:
parts and their libraries:
microbuilder: This work is placed in the public domain, and may be freely used for commercial and non-commercial work with the following conditions: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
SparkFun-Jumpers: Licensing: Creative Commons ShareAlike 4.0 International - https://creativecommons.org/licenses/by-sa/4.0
